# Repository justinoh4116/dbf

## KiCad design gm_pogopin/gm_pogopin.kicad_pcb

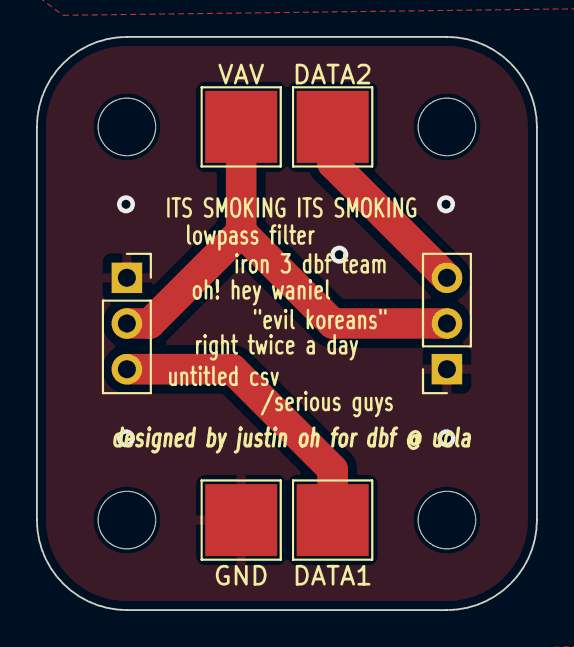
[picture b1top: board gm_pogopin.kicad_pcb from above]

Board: 2 copper layers, 27.8 x 31.8 mm, 10 parts (0 on the bottom side), 4 nets.

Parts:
DATA1: DATA1; TestPoint_Pad_4.0x4.0mm
DATA2: DATA2; TestPoint_Pad_4.0x4.0mm
GND: GND; TestPoint_Pad_4.0x4.0mm
H1, H2, H3, H4: MountingHole; MountingHole_3.2mm_M3
J1: SERVO1; PinSocket_1x03_P2.54mm_Vertical
J2: SERVO2; PinSocket_1x03_P2.54mm_Vertical
VAV: V_AV; TestPoint_Pad_4.0x4.0mm

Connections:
/DATA1: DATA1.1, J1.3
/DATA2: DATA2.1, J2.3
GND: GND.1, J1.1, J2.1
VCC: J1.2, J2.2, VAV.1

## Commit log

2025-11-06 4 -> 5 channels
2025-11-27 jafdsklfjasdfjasdlf
2025-11-27 Add README with wiring and setup instructions
    Added detailed wiring and setup instructions for the pixhawk load cell logging system, including connections for the load cell, pre-amp, and power module.
2026-01-16 update pixhawk status messages
2026-01-16 remove post-processing of adc values
2026-01-16 initial load cell calibration script
2026-01-17 updated cal script & cal gains
2026-01-18 lowered arduino -> pixhawk data rate
2026-01-31 adjusted y gain
